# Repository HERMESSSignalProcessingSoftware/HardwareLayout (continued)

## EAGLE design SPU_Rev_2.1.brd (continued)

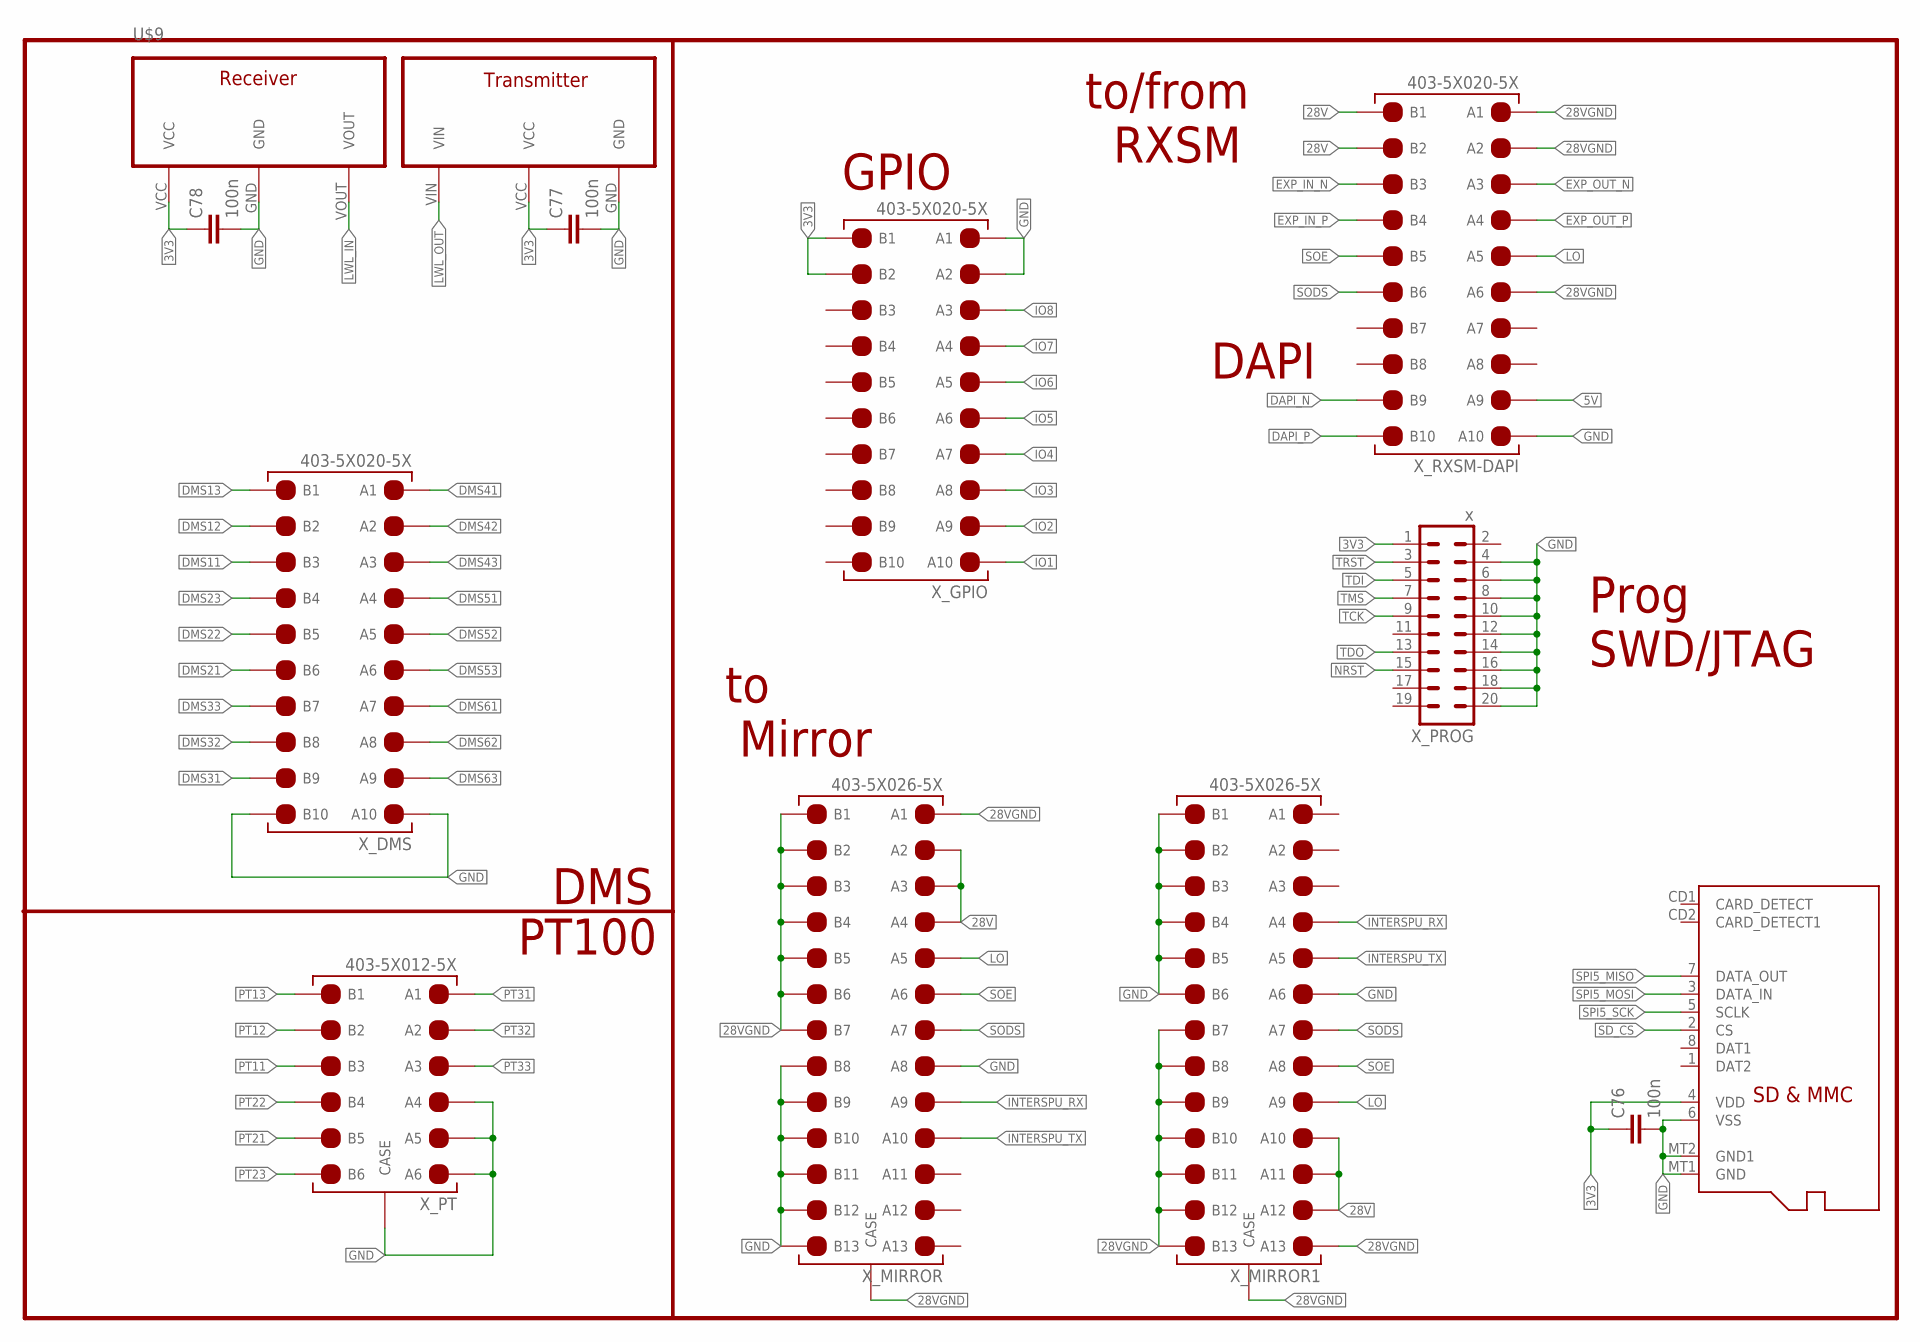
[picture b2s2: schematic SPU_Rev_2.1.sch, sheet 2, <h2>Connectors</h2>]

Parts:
C76: 100n; 0603-CAP
C77, C78: 100n; C1206
U$7: MICROSD
U$8: PLT131PLT131-T1; PLT131-T1
U$9: PLR135; PLR135-T1
X_DMS: 403-5X020-5X
X_GPIO: 403-5X020-5X
X_MIRROR, X_MIRROR1: 403-5X026-5X
X_PROG: x; MA10-2
X_PT: 403-5X012-5X
X_RXSM-DAPI: 403-5X020-5X

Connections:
3V3: C76.1, C77.1, C78.1, U$7.4 (VDD), U$8.VCC, U$9.VCC, X_GPIO.P$B1 (B1), X_GPIO.P$B2 (B2), X_PROG.1; also elsewhere on the board
5V: X_RXSM-DAPI.P$A9 (A9); also elsewhere on the board
28V: X_MIRROR.P$A2 (A2), X_MIRROR.P$A3 (A3), X_MIRROR.P$A4 (A4), X_MIRROR1.P$A10 (A10), X_MIRROR1.P$A11 (A11), X_MIRROR1.P$A12 (A12), X_RXSM-DAPI.P$B1 (B1), X_RXSM-DAPI.P$B2 (B2); also elsewhere on the board
28VGND: X_MIRROR.P$A1 (A1), X_MIRROR.P$B1 (B1), X_MIRROR.P$B2 (B2), X_MIRROR.P$B3 (B3), X_MIRROR.P$B4 (B4), X_MIRROR.P$B5 (B5), X_MIRROR.P$B6 (B6), X_MIRROR.P$B7 (B7), X_MIRROR.P$BL1 (CASE), X_MIRROR.P$BL2 (CASE), X_MIRROR.P$BL3 (CASE), X_MIRROR.P$BL4 (CASE), X_MIRROR1.P$A13 (A13), X_MIRROR1.P$B7 (B7), X_MIRROR1.P$B8 (B8), X_MIRROR1.P$B9 (B9), X_MIRROR1.P$B10 (B10), X_MIRROR1.P$B11 (B11), X_MIRROR1.P$B12 (B12), X_MIRROR1.P$B13 (B13), X_MIRROR1.P$BL1 (CASE), X_MIRROR1.P$BL2 (CASE), X_MIRROR1.P$BL3 (CASE), X_MIRROR1.P$BL4 (CASE), X_RXSM-DAPI.P$A1 (A1), X_RXSM-DAPI.P$A2 (A2), X_RXSM-DAPI.P$A6 (A6); also elsewhere on the board
DAPI_N: X_RXSM-DAPI.P$B9 (B9); also elsewhere on the board
DAPI_P: X_RXSM-DAPI.P$B10 (B10); also elsewhere on the board
DMS11: X_DMS.P$B3 (B3); also elsewhere on the board
DMS12: X_DMS.P$B2 (B2); also elsewhere on the board
DMS13: X_DMS.P$B1 (B1); also elsewhere on the board
DMS21: X_DMS.P$B6 (B6); also elsewhere on the board
DMS22: X_DMS.P$B5 (B5); also elsewhere on the board
DMS23: X_DMS.P$B4 (B4); also elsewhere on the board
DMS31: X_DMS.P$B9 (B9); also elsewhere on the board
DMS32: X_DMS.P$B8 (B8); also elsewhere on the board
DMS33: X_DMS.P$B7 (B7); also elsewhere on the board
DMS41: X_DMS.P$A1 (A1); also elsewhere on the board
DMS42: X_DMS.P$A2 (A2); also elsewhere on the board
DMS43: X_DMS.P$A3 (A3); also elsewhere on the board
DMS51: X_DMS.P$A4 (A4); also elsewhere on the board
DMS52: X_DMS.P$A5 (A5); also elsewhere on the board
DMS53: X_DMS.P$A6 (A6); also elsewhere on the board
DMS61: X_DMS.P$A7 (A7); also elsewhere on the board
DMS62: X_DMS.P$A8 (A8); also elsewhere on the board
DMS63: X_DMS.P$A9 (A9); also elsewhere on the board
EXP_IN_N: X_RXSM-DAPI.P$B3 (B3); also elsewhere on the board
EXP_IN_P: X_RXSM-DAPI.P$B4 (B4); also elsewhere on the board
EXP_OUT_N: X_RXSM-DAPI.P$A3 (A3); also elsewhere on the board
EXP_OUT_P: X_RXSM-DAPI.P$A4 (A4); also elsewhere on the board
GND: C76.2, C77.2, C78.2, U$7.6 (VSS), U$7.MT1 (GND), U$7.MT2 (GND1), U$8.GND, U$9.GND, X_DMS.P$A10 (A10), X_DMS.P$B10 (B10), X_GPIO.P$A1 (A1), X_GPIO.P$A2 (A2), X_MIRROR.P$A8 (A8), X_MIRROR.P$B8 (B8), X_MIRROR.P$B9 (B9), X_MIRROR.P$B10 (B10), X_MIRROR.P$B11 (B11), X_MIRROR.P$B12 (B12), X_MIRROR.P$B13 (B13), X_MIRROR1.P$A6 (A6), X_MIRROR1.P$B1 (B1), X_MIRROR1.P$B2 (B2), X_MIRROR1.P$B3 (B3), X_MIRROR1.P$B4 (B4), X_MIRROR1.P$B5 (B5), X_MIRROR1.P$B6 (B6), X_PROG.4, X_PROG.6, X_PROG.8, X_PROG.10, X_PROG.12, X_PROG.14, X_PROG.16, X_PROG.18, X_PROG.20, X_PT.P$A4 (A4), X_PT.P$A5 (A5), X_PT.P$A6 (A6), X_PT.P$BL1 (CASE), X_PT.P$BL2 (CASE), X_PT.P$BL3 (CASE), X_PT.P$BL4 (CASE), X_RXSM-DAPI.P$A10 (A10); also elsewhere on the board
INTERSPU_RX: X_MIRROR.P$A9 (A9), X_MIRROR1.P$A4 (A4); also elsewhere on the board
INTERSPU_TX: X_MIRROR.P$A10 (A10), X_MIRROR1.P$A5 (A5); also elsewhere on the board
IO1: X_GPIO.P$A10 (A10); also elsewhere on the board
IO2: X_GPIO.P$A9 (A9); also elsewhere on the board
IO3: X_GPIO.P$A8 (A8); also elsewhere on the board
IO4: X_GPIO.P$A7 (A7); also elsewhere on the board
IO5: X_GPIO.P$A6 (A6); also elsewhere on the board
IO6: X_GPIO.P$A5 (A5); also elsewhere on the board
IO7: X_GPIO.P$A4 (A4); also elsewhere on the board
IO8: X_GPIO.P$A3 (A3); also elsewhere on the board
LO: X_MIRROR.P$A5 (A5), X_MIRROR1.P$A9 (A9), X_RXSM-DAPI.P$A5 (A5); also elsewhere on the board
LWL_IN: U$9.VOUT; also elsewhere on the board
LWL_OUT: U$8.VIN; also elsewhere on the board
NRST: X_PROG.15; also elsewhere on the board
PT11: X_PT.P$B3 (B3); also elsewhere on the board
PT12: X_PT.P$B2 (B2); also elsewhere on the board
PT13: X_PT.P$B1 (B1); also elsewhere on the board
PT21: X_PT.P$B5 (B5); also elsewhere on the board
PT22: X_PT.P$B4 (B4); also elsewhere on the board
PT23: X_PT.P$B6 (B6); also elsewhere on the board
PT31: X_PT.P$A1 (A1); also elsewhere on the board
PT32: X_PT.P$A2 (A2); also elsewhere on the board
PT33: X_PT.P$A3 (A3); also elsewhere on the board
SD_CS: U$7.2 (CS); also elsewhere on the board
SODS: X_MIRROR.P$A7 (A7), X_MIRROR1.P$A7 (A7), X_RXSM-DAPI.P$B6 (B6); also elsewhere on the board
SOE: X_MIRROR.P$A6 (A6), X_MIRROR1.P$A8 (A8), X_RXSM-DAPI.P$B5 (B5); also elsewhere on the board
SPI5_MISO: U$7.7 (DATA_OUT); also elsewhere on the board
SPI5_MOSI: U$7.3 (DATA_IN); also elsewhere on the board
SPI5_SCK: U$7.5 (SCLK); also elsewhere on the board
TCK: X_PROG.9; also elsewhere on the board
TDI: X_PROG.5; also elsewhere on the board
TDO: X_PROG.13; also elsewhere on the board
TMS: X_PROG.7; also elsewhere on the board
TRST: X_PROG.3; also elsewhere on the board

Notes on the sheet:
DMS
PT100
DAPI
to/from RXSM
to Mirror
Prog SWD/JTAG
GPIO

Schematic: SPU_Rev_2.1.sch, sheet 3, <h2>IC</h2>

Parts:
C1, C2: 22p; C0603
C3, C5, C6, C7, C8, C9, C10, C12, C13, C14, C15, C19, C21, C22, C23, C24, C25, C27, C45, C46, C47, C48, C50, C51, C53, C54, C55, C57, C58, C59: 100n; C0603
C4, C11, C20, C26, C49, C56: 1u; C1206
C28, C29, C30, C31, C32, C33, C34, C35, C36, C37, C42, C43, C75: 100n; C0805
C38, C39, C40, C41, C60, C61, C62, C64, C65, C66, C67, C68, C69, C70, C71, C72, C73: 10u; E/7260-38W
C44: ~0; C0805
C52, C74: 10n; C0805
C_AVDD_PT1, C_AVDD_PT2, C_AVDD_PT3: 100n; C0603
C_DVDD_PT1, C_DVDD_PT2, C_DVDD_PT3: 100n; C0603
C_ICM1_PT1, C_ICM1_PT2, C_ICM2_PT1, C_ICM2_PT2: C-EUC0603; C0603
C_ICM1_PT3, C_ICM2_PT3: 4n7; C0603
C_IDIFF_PT1, C_IDIFF_PT2: C-EUC0603; C0603
C_IDIFF_PT3: 47n; C0603
C_RCM1_PT1, C_RCM1_PT2, C_RCM1_PT3, C_RCM2_PT1, C_RCM2_PT2, C_RCM2_PT3: C-EUC0603; C0603
C_RDIFF_PT1, C_RDIFF_PT2: C-EUC0603; C0603
C_RDIFF_PT3: 100n; C0603
C_VREF_PT1, C_VREF_PT2, C_VREF_PT3: 1u; C0603
D1, D2, D5, D6: 6V; DMELF
D3, D4, D7, D8, D9, D10, D11, D12: 3V6; DMELF
Q1: 12MHz; SM49
R1, R2, R8, R30, R36, R37, R43, R44, R50, R51, R57, R58: 4k7; R0603
R3, R31, R38, R45, R52, R59: 47; R0603
R4, R5, R32, R33, R39, R40, R46, R47, R53, R54, R60, R61: 40 1%; R0805
R6, R7, R34, R35, R41, R42, R48, R49, R55, R56, R62, R63: 1k 0.1%; R0805
R10, R15: 500; R0805
R11: 3k; R0805
R12: 2k; R0805
R13: 4k7; R0805
R14: 7k5; R0805
R16, R17: 3k3; R0805
R22: 100k; R0805
R23: 1k; R0805
R24, R25: ?; R0805
RN11: 3k; EXBS8V
RN12: 1k; EXBS8V
RN_A_PT1, RN_A_PT2, RN_A_PT3: 47; 0603-ARC
RN_B_PT1, RN_B_PT2, RN_B_PT3: 47; 0603-ARC
RN_DMS1, RN_DMS2, RN_DMS3, RN_DMS4, RN_DMS5, RN_DMS6: 47; 0603-ARC
R_I1_PT1, R_I1_PT2, R_I2_PT1, R_I2_PT2: R-EU_R0603; R0603
R_I1_PT3, R_I2_PT3: 5k; R0603
R_R1_PT1, R_R1_PT2, R_R2_PT1, R_R2_PT2: R-EU_R0603; R0603
R_R1_PT3: 3k16; R0603
R_R2_PT3: inf; R0603
R_REF_PT1, R_REF_PT2: R-EU_R0603; R0603
R_REF_PT3: 1k62; R0603
U$1, U$2, U$3, U$4, U$5, U$6: COMMON_MODE_CHOKE
U_7805: LM78L05ACMX/NOPB; SOIC8
U_ADC_DMS1, U_ADC_DMS2, U_ADC_DMS3, U_ADC_DMS4, U_ADC_DMS5, U_ADC_DMS6: ADS1147TSSOP20; TSSOP20
U_ADC_PT1, U_ADC_PT2, U_ADC_PT3: ADS1147TSSOP20; TSSOP20
U_ADR366_3: ADR366WAUJZ; SOT23-5
U_CH340G: CH340G; SOIC16
U_FLASH1, U_FLASH2: S70FL01GS; SO16
U_LT1528: LT1528; Q5-DD
U_MAX488: MAX488CSA; SO08
U_OPTO_1, U_OPTO_2, U_OPTO_3: MOCD207MSOIC-8; SOIC127P594X363-8N
U_TRACODCDC: THN10-2411WIR; THL_20WI_SERIES

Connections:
3V3: C3.1, C5.1, C9.1, C10.1, C15.1, C19.1, C24.1, C25.1, C28.1, C29.1, C30.1, C31.1, C32.1, C33.1, C37.2, C41.+, C47.1, C48.1, C54.1, C55.1, C67.+, C68.+, C69.+, C70.+, C71.+, C72.+, C73.+, C_AVDD_PT1.1, C_AVDD_PT2.1, C_AVDD_PT3.1, C_DVDD_PT1.1, C_DVDD_PT2.1, C_DVDD_PT3.1, R1.1, R2.2, R6.2, R8.1, R13.2, R30.2, R34.2, R36.1, R37.2, R41.2, R43.1, R44.2, R48.2, R50.1, R51.2, R55.2, R57.1, R58.2, R62.2, RN12.1, RN12.2 (1), RN12.3 (1), RN12.4 (1), RN_A_PT1.8 (2), RN_A_PT2.8 (2), RN_A_PT3.8 (2), RN_B_PT1.6 (2), RN_B_PT2.6 (2), RN_B_PT3.6 (2), U$1.P$2 (2), U$2.P$2 (2), U$3.P$2 (2), U$4.P$2 (2), U$5.P$2 (2), U$6.P$2 (2), U_ADC_DMS1.1 (DVDD), U_ADC_DMS1.14 (AVDD), U_ADC_DMS2.1 (DVDD), U_ADC_DMS2.14 (AVDD), U_ADC_DMS3.1 (DVDD), U_ADC_DMS3.14 (AVDD), U_ADC_DMS4.1 (DVDD), U_ADC_DMS4.14 (AVDD), U_ADC_DMS5.1 (DVDD), U_ADC_DMS5.14 (AVDD), U_ADC_DMS6.1 (DVDD), U_ADC_DMS6.14 (AVDD), U_ADC_PT1.1 (DVDD), U_ADC_PT1.14 (AVDD), U_ADC_PT2.1 (DVDD), U_ADC_PT2.14 (AVDD), U_ADC_PT3.1 (DVDD), U_ADC_PT3.14 (AVDD), U_CH340G.4 (V3), U_CH340G.16 (VCC), U_FLASH1.2 (VCC), U_FLASH2.2 (VCC), U_LT1528.1 (OUT), U_LT1528.2 (SENSE); also elsewhere on the board
3V3REF: C74.2, C75.2, R24.2, U_ADR366_3.4 (VOUT); also elsewhere on the board
5V: C35.2, C36.2, C39.+, C40.+, C52.2, C64.+, C65.+, C66.+, U_ADR366_3.3 (VIN), U_LT1528.4 (SHDN), U_LT1528.5 (IN), U_TRACODCDC.3 (+VOUT); also elsewhere on the board
5V-28V: C43.1, R14.2, R16.1, U_7805.1 (VOUT), U_MAX488.1 (VCC); also elsewhere on the board
28V: C34.2, C38.+, C42.2, C60.+, C61.+, C62.+, RN11.1, RN11.2 (1), RN11.3 (1), RN11.4 (1), U_7805.8 (VIN), U_TRACODCDC.1 (+VIN); also elsewhere on the board
28VGND: C34.1, C38.-, C42.1, C43.2, C44.2, C60.-, C61.-, C62.-, D5.A, D6.A, R11.1, R17.1, U_7805.2 (GND), U_7805.3 (GND), U_7805.6 (GND), U_7805.7 (GND), U_MAX488.4 (GND), U_OPTO_3.5 (EMT2), U_TRACODCDC.2 (-VIN); also elsewhere on the board
!CS!_DMS1: R3.2; also elsewhere on the board
!CS!_DMS2: R31.2; also elsewhere on the board
!CS!_DMS3: R38.2; also elsewhere on the board
!CS!_DMS4: R45.2; also elsewhere on the board
!CS!_DMS5: R52.2; also elsewhere on the board
!CS!_DMS6: R59.2; also elsewhere on the board
!CS!_PT1: RN_B_PT1.7 (2); also elsewhere on the board
!CS!_PT2: RN_B_PT2.7 (2); also elsewhere on the board
!CS!_PT3: RN_B_PT3.7 (2); also elsewhere on the board
!DRDY!_DMS1: RN_DMS1.5 (2); also elsewhere on the board
!DRDY!_DMS2: RN_DMS2.5 (2); also elsewhere on the board
!DRDY!_DMS3: RN_DMS3.5 (2); also elsewhere on the board
!DRDY!_DMS4: RN_DMS4.5 (2); also elsewhere on the board
!DRDY!_DMS5: RN_DMS5.5 (2); also elsewhere on the board
!DRDY!_DMS6: RN_DMS6.5 (2); also elsewhere on the board
!DRDY!_PT1: RN_B_PT1.8 (2); also elsewhere on the board
!DRDY!_PT2: RN_B_PT2.8 (2); also elsewhere on the board
!DRDY!_PT3: RN_B_PT3.8 (2); also elsewhere on the board
DAPI_N: D1.C, U_CH340G.6 (D-); also elsewhere on the board
DAPI_P: D2.C, U_CH340G.5 (D+); also elsewhere on the board
DAPI_RX: D4.C, U_CH340G.2 (TX); also elsewhere on the board
DAPI_TX: D3.C, U_CH340G.3 (RX); also elsewhere on the board
DMS11: U$2.P$1 (1); also elsewhere on the board
DMS12: U$2.P$3 (3); also elsewhere on the board
DMS13: U$2.P$5 (5); also elsewhere on the board
DMS21: U$1.P$1 (1); also elsewhere on the board
DMS22: U$1.P$3 (3); also elsewhere on the board
DMS23: U$1.P$5 (5); also elsewhere on the board
DMS31: U$3.P$1 (1); also elsewhere on the board
DMS32: U$3.P$3 (3); also elsewhere on the board
DMS33: U$3.P$5 (5); also elsewhere on the board
DMS41: U$4.P$1 (1); also elsewhere on the board
DMS42: U$4.P$3 (3); also elsewhere on the board
DMS43: U$4.P$5 (5); also elsewhere on the board
DMS51: U$5.P$1 (1); also elsewhere on the board
DMS52: U$5.P$3 (3); also elsewhere on the board
DMS53: U$5.P$5 (5); also elsewhere on the board
DMS61: U$6.P$1 (1); also elsewhere on the board
DMS62: U$6.P$3 (3); also elsewhere on the board
DMS63: U$6.P$5 (5); also elsewhere on the board
EXP_IN: D5.C, U_MAX488.2 (RO), U_OPTO_3.1 (A1)
EXP_IN_N: R15.1, R17.2, U_MAX488.7 (B); also elsewhere on the board
EXP_IN_OPT: D10.C, R13.1, U_OPTO_3.8 (COL1); also elsewhere on the board
EXP_IN_P: R10.2, R16.2, U_MAX488.8 (A); also elsewhere on the board
EXP_OUT: D6.C, R14.1, U_MAX488.3 (DI), U_OPTO_3.6 (COL2)
EXP_OUT_N: U_MAX488.6 (Z); also elsewhere on the board
EXP_OUT_OPT: U_OPTO_3.3 (A2); also elsewhere on the board
EXP_OUT_P: U_MAX488.5 (Y); also elsewhere on the board
FL_1_CS1: U_FLASH1.7 (CS1); also elsewhere on the board
FL_1_CS2: U_FLASH1.6 (CS2); also elsewhere on the board
FL_1_HLD: U_FLASH1.1 (HOLD); also elsewhere on the board
FL_1_RES: U_FLASH1.3 (RESET); also elsewhere on the board
FL_1_WP: U_FLASH1.9 (WP); also elsewhere on the board
FL_2_CS1: U_FLASH2.7 (CS1); also elsewhere on the board
FL_2_CS2: U_FLASH2.6 (CS2); also elsewhere on the board
FL_2_HLD: U_FLASH2.1 (HOLD); also elsewhere on the board
FL_2_RES: U_FLASH2.3 (RESET); also elsewhere on the board
FL_2_WP: U_FLASH2.9 (WP); also elsewhere on the board
GND: C1.2, C2.2, C3.2, C4.2, C5.2, C6.1, C8.2, C9.2, C10.2, C11.2, C12.1, C14.2, C15.2, C19.2, C20.2, C21.1, C23.2, C24.2, C25.2, C26.2, C27.1, C28.2, C29.2, C30.2, C31.2, C32.2, C33.2, C35.1, C36.1, C37.1, C39.-, C40.-, C41.-, C46.2, C47.2, C48.2, C49.2, C50.1, C52.1, C53.2, C54.2, C55.2, C56.2, C57.1, C59.2, C64.-, C65.-, C66.-, C67.-, C68.-, C69.-, C70.-, C71.-, C72.-, C73.-, C74.1, C75.1, C_AVDD_PT1.2, C_AVDD_PT2.2, C_AVDD_PT3.2, C_DVDD_PT1.2, C_DVDD_PT2.2, C_DVDD_PT3.2, C_ICM1_PT1.1, C_ICM1_PT2.1, C_ICM1_PT3.1, C_ICM2_PT1.2, C_ICM2_PT2.2, C_ICM2_PT3.2, C_RCM1_PT1.1, C_RCM1_PT2.1, C_RCM1_PT3.1, C_RCM2_PT1.2, C_RCM2_PT2.2, C_RCM2_PT3.2, C_VREF_PT1.2, C_VREF_PT2.2, C_VREF_PT3.2, D1.A, D2.A, D3.A, D4.A, D7.A, D8.A, D9.A, D10.A, D11.A, D12.A, R7.2, R12.1, R23.1, R35.2, R42.2, R49.2, R56.2, R63.2, RN_B_PT1.4 (1), RN_B_PT1.5 (2), RN_B_PT2.4 (1), RN_B_PT2.5 (2), RN_B_PT3.4 (1), RN_B_PT3.5 (2), R_R2_PT1.2, R_R2_PT2.2, R_R2_PT3.2, R_REF_PT1.1, R_REF_PT2.1, R_REF_PT3.1, U$1.P$6 (6), U$2.P$6 (6), U$3.P$6 (6), U$4.P$6 (6), U$5.P$6 (6), U$6.P$6 (6), U_ADC_DMS1.2 (DGND/DSS), U_ADC_DMS1.3 (CLK), U_ADC_DMS1.8 (VREFCOM), U_ADC_DMS1.13 (AVSS), U_ADC_DMS2.2 (DGND/DSS), U_ADC_DMS2.3 (CLK), U_ADC_DMS2.8 (VREFCOM), U_ADC_DMS2.13 (AVSS), U_ADC_DMS3.2 (DGND/DSS), U_ADC_DMS3.3 (CLK), U_ADC_DMS3.8 (VREFCOM), U_ADC_DMS3.13 (AVSS), U_ADC_DMS4.2 (DGND/DSS), U_ADC_DMS4.3 (CLK), U_ADC_DMS4.8 (VREFCOM), U_ADC_DMS4.13 (AVSS), U_ADC_DMS5.2 (DGND/DSS), U_ADC_DMS5.3 (CLK), U_ADC_DMS5.8 (VREFCOM), U_ADC_DMS5.13 (AVSS), U_ADC_DMS6.2 (DGND/DSS), U_ADC_DMS6.3 (CLK), U_ADC_DMS6.8 (VREFCOM), U_ADC_DMS6.13 (AVSS), U_ADC_PT1.2 (DGND/DSS), U_ADC_PT1.3 (CLK), U_ADC_PT1.8 (VREFCOM), U_ADC_PT1.13 (AVSS), U_ADC_PT2.2 (DGND/DSS), U_ADC_PT2.3 (CLK), U_ADC_PT2.8 (VREFCOM), U_ADC_PT2.13 (AVSS), U_ADC_PT3.2 (DGND/DSS), U_ADC_PT3.3 (CLK), U_ADC_PT3.8 (VREFCOM), U_ADC_PT3.13 (AVSS), U_ADR366_3.2 (GND), U_CH340G.1 (GND), U_FLASH1.10 (VSS), U_FLASH2.10 (VSS), U_LT1528.3 (GND), U_LT1528.6 (GND), U_OPTO_1.5 (EMT2), U_OPTO_1.7 (EMT1), U_OPTO_2.5 (EMT2), U_OPTO_2.7 (EMT1), U_OPTO_3.7 (EMT1), U_TRACODCDC.5 (-VOUT); also elsewhere on the board
INTERSPU_RX: D11.C; also elsewhere on the board
INTERSPU_TX: D12.C; also elsewhere on the board
LO: U_OPTO_2.2 (C1); also elsewhere on the board
LO_OPT: D7.C, RN12.6 (2), U_OPTO_2.8 (COL1); also elsewhere on the board
unnamed: C2.1, Q1.2, U_CH340G.8 (XO)
unnamed: R2.1, U_ADC_DMS1.15 (START)
unnamed: C1.1, Q1.1, U_CH340G.7 (XI)
unnamed: C_RCM2_PT2.1, C_RDIFF_PT2.2, R_R2_PT2.1, U_ADC_PT2.6 (REFN0/GPIO1)
unnamed: C_RCM1_PT2.2, C_RDIFF_PT2.1, R_R1_PT2.1, U_ADC_PT2.5 (REFP0/GPIO0)
unnamed: C_ICM2_PT2.1, C_IDIFF_PT2.2, R_I2_PT2.1, U_ADC_PT2.11 (AIN2/IEXC/GPIO2)
unnamed: C12.2, C13.1, R32.1, U_ADC_DMS2.9 (AIN0/IEXC)
unnamed: C_VREF_PT1.1, U_ADC_PT1.7 (VREFOUT)
unnamed: C_ICM2_PT1.1, C_IDIFF_PT1.2, R_I2_PT1.1, U_ADC_PT1.11 (AIN2/IEXC/GPIO2)
unnamed: RN_DMS1.1, U_ADC_DMS1.20 (SCLK)
unnamed: C13.2, C14.1, R33.1, U_ADC_DMS2.10 (AIN1/IEXC)
unnamed: R33.2, R34.1, R35.1
unnamed: C_RCM2_PT1.1, C_RDIFF_PT1.2, R_R2_PT1.1, U_ADC_PT1.6 (REFN0/GPIO1)
unnamed: C_RCM1_PT1.2, C_RDIFF_PT1.1, R_R1_PT1.1, U_ADC_PT1.5 (REFP0/GPIO0)
unnamed: C_ICM1_PT1.2, C_IDIFF_PT1.1, R_I1_PT1.1, U_ADC_PT1.10 (AIN1/IEXC)
unnamed: RN_A_PT1.2 (1), U_ADC_PT1.20 (SCLK)
unnamed 101: U_TRACODCDC.4 (TRIM); also elsewhere on the board
unnamed: RN_A_PT1.3 (1), U_ADC_PT1.19 (DIN)
unnamed: RN_A_PT1.4 (1), U_ADC_PT1.18 (DOUT/!DRDY)
unnamed: C_ICM1_PT2.2, C_IDIFF_PT2.1, R_I1_PT2.1, U_ADC_PT2.10 (AIN1/IEXC)
unnamed: C_VREF_PT2.1, U_ADC_PT2.7 (VREFOUT)
unnamed: RN_A_PT2.2 (1), U_ADC_PT2.20 (SCLK)
unnamed: RN_B_PT1.1, U_ADC_PT1.17 (!DRDY)
unnamed: RN_B_PT1.2 (1), U_ADC_PT1.16 (!CS)
unnamed: RN_B_PT1.3 (1), U_ADC_PT1.15 (START)
unnamed: RN_A_PT2.3 (1), U_ADC_PT2.19 (DIN)
unnamed: RN_A_PT2.4 (1), U_ADC_PT2.18 (DOUT/!DRDY)
unnamed: RN_B_PT2.1, U_ADC_PT2.17 (!DRDY)
unnamed: RN_B_PT2.2 (1), U_ADC_PT2.16 (!CS)
unnamed: RN_B_PT2.3 (1), U_ADC_PT2.15 (START)
unnamed: C_RCM2_PT3.1, C_RDIFF_PT3.2, R_R2_PT3.1, U_ADC_PT3.6 (REFN0/GPIO1)
unnamed: C_RCM1_PT3.2, C_RDIFF_PT3.1, R_R1_PT3.1, U_ADC_PT3.5 (REFP0/GPIO0)
unnamed: RN11.6 (2), U_OPTO_1.1 (A1)
unnamed: RN11.5 (2), U_OPTO_1.3 (A2)
unnamed: R12.2, U_OPTO_3.4 (C2)
unnamed: RN12.5 (2), U_OPTO_2.6 (COL2)
unnamed: RN11.8 (2), U_OPTO_2.1 (A1)
unnamed: RN11.7 (2), U_OPTO_2.3 (A2)
unnamed: R11.2, U_OPTO_3.2 (C1)
unnamed: C44.1, R10.1, R15.2
unnamed: C_ICM2_PT3.1, C_IDIFF_PT3.2, R_I2_PT3.1, U_ADC_PT3.11 (AIN2/IEXC/GPIO2)
unnamed: C_ICM1_PT3.2, C_IDIFF_PT3.1, R_I1_PT3.1, U_ADC_PT3.10 (AIN1/IEXC)
unnamed: C_VREF_PT3.1, U_ADC_PT3.7 (VREFOUT)
unnamed: RN_A_PT3.2 (1), U_ADC_PT3.20 (SCLK)
unnamed: RN_A_PT3.3 (1), U_ADC_PT3.19 (DIN)
unnamed: RN_A_PT3.4 (1), U_ADC_PT3.18 (DOUT/!DRDY)
unnamed: RN_B_PT3.1, U_ADC_PT3.17 (!DRDY)
unnamed: RN_B_PT3.2 (1), U_ADC_PT3.16 (!CS)
unnamed: RN_B_PT3.3 (1), U_ADC_PT3.15 (START)
unnamed: RN_A_PT3.1, U_ADC_PT3.4 (!RESET)
unnamed: RN_A_PT2.1, U_ADC_PT2.4 (!RESET)
unnamed: RN_A_PT1.1, U_ADC_PT1.4 (!RESET)
unnamed: C11.1, U_ADC_DMS2.7 (VREFOUT)
unnamed: R22.1, U_ADR366_3.5 (TRIM)
unnamed: R22.2, R24.1, R25.2
unnamed: R23.2, R25.1
unnamed: R32.2, U$1.P$4 (4)
unnamed: R1.2, U_ADC_DMS1.4 (!RESET)
unnamed: RN_DMS1.2 (1), U_ADC_DMS1.19 (DIN)
unnamed: RN_DMS1.3 (1), U_ADC_DMS1.18 (DOUT/!DRDY)
unnamed: RN_DMS1.4 (1), U_ADC_DMS1.17 (!DRDY)
unnamed: R3.1, U_ADC_DMS1.16 (!CS)
unnamed: R8.2, U_ADC_DMS2.4 (!RESET)
unnamed: R30.1, U_ADC_DMS2.15 (START)
unnamed: C6.2, C7.1, R4.1, U_ADC_DMS1.9 (AIN0/IEXC)
unnamed: C7.2, C8.1, R5.1, U_ADC_DMS1.10 (AIN1/IEXC)
unnamed: R5.2, R6.1, R7.1
unnamed: C4.1, U_ADC_DMS1.7 (VREFOUT)
unnamed: R4.2, U$2.P$4 (4)
unnamed: RN_DMS2.1, U_ADC_DMS2.20 (SCLK)
unnamed: RN_DMS2.2 (1), U_ADC_DMS2.19 (DIN)
unnamed: RN_DMS2.3 (1), U_ADC_DMS2.18 (DOUT/!DRDY)
unnamed: RN_DMS2.4 (1), U_ADC_DMS2.17 (!DRDY)
unnamed: R31.1, U_ADC_DMS2.16 (!CS)
unnamed: C21.2, C22.1, R39.1, U_ADC_DMS3.9 (AIN0/IEXC)
unnamed: C22.2, C23.1, R40.1, U_ADC_DMS3.10 (AIN1/IEXC)
unnamed: R40.2, R41.1, R42.1
unnamed: C20.1, U_ADC_DMS3.7 (VREFOUT)
unnamed: R39.2, U$3.P$4 (4)
unnamed: R36.2, U_ADC_DMS3.4 (!RESET)
unnamed: R37.1, U_ADC_DMS3.15 (START)
unnamed: RN_DMS3.1, U_ADC_DMS3.20 (SCLK)
unnamed: RN_DMS3.2 (1), U_ADC_DMS3.19 (DIN)
unnamed: RN_DMS3.3 (1), U_ADC_DMS3.18 (DOUT/!DRDY)
unnamed: RN_DMS3.4 (1), U_ADC_DMS3.17 (!DRDY)
unnamed: R38.1, U_ADC_DMS3.16 (!CS)
unnamed: C27.2, C45.1, R46.1, U_ADC_DMS4.9 (AIN0/IEXC)
unnamed: C45.2, C46.1, R47.1, U_ADC_DMS4.10 (AIN1/IEXC)
unnamed: R47.2, R48.1, R49.1
unnamed: C26.1, U_ADC_DMS4.7 (VREFOUT)
unnamed: R46.2, U$4.P$4 (4)
unnamed: R43.2, U_ADC_DMS4.4 (!RESET)
unnamed: R44.1, U_ADC_DMS4.15 (START)
unnamed: RN_DMS4.1, U_ADC_DMS4.20 (SCLK)
unnamed: RN_DMS4.2 (1), U_ADC_DMS4.19 (DIN)
unnamed: RN_DMS4.3 (1), U_ADC_DMS4.18 (DOUT/!DRDY)
unnamed: RN_DMS4.4 (1), U_ADC_DMS4.17 (!DRDY)
unnamed: R45.1, U_ADC_DMS4.16 (!CS)
unnamed: C50.2, C51.1, R53.1, U_ADC_DMS5.9 (AIN0/IEXC)
unnamed: C51.2, C53.1, R54.1, U_ADC_DMS5.10 (AIN1/IEXC)
unnamed: R54.2, R55.1, R56.1
unnamed: C49.1, U_ADC_DMS5.7 (VREFOUT)
unnamed: R53.2, U$5.P$4 (4)
unnamed: R50.2, U_ADC_DMS5.4 (!RESET)
unnamed: R51.1, U_ADC_DMS5.15 (START)
unnamed: RN_DMS5.1, U_ADC_DMS5.20 (SCLK)
unnamed: RN_DMS5.2 (1), U_ADC_DMS5.19 (DIN)
unnamed: RN_DMS5.3 (1), U_ADC_DMS5.18 (DOUT/!DRDY)
unnamed: RN_DMS5.4 (1), U_ADC_DMS5.17 (!DRDY)
unnamed: R52.1, U_ADC_DMS5.16 (!CS)
unnamed: C57.2, C58.1, R60.1, U_ADC_DMS6.9 (AIN0/IEXC)
unnamed: C58.2, C59.1, R61.1, U_ADC_DMS6.10 (AIN1/IEXC)
unnamed: R61.2, R62.1, R63.1
unnamed: C56.1, U_ADC_DMS6.7 (VREFOUT)
unnamed: R60.2, U$6.P$4 (4)
unnamed: R57.2, U_ADC_DMS6.4 (!RESET)
unnamed: R58.1, U_ADC_DMS6.15 (START)
unnamed: RN_DMS6.1, U_ADC_DMS6.20 (SCLK)
unnamed: RN_DMS6.2 (1), U_ADC_DMS6.19 (DIN)
unnamed: RN_DMS6.3 (1), U_ADC_DMS6.18 (DOUT/!DRDY)
unnamed: RN_DMS6.4 (1), U_ADC_DMS6.17 (!DRDY)
unnamed: R59.1, U_ADC_DMS6.16 (!CS)
PT11: R_I1_PT1.2, U_ADC_PT1.9 (AIN0/IEXC); also elsewhere on the board
PT12: R_I2_PT1.2, U_ADC_PT1.12 (AIN3/IEXC/GPIO3); also elsewhere on the board
PT13: R_R1_PT1.2, R_REF_PT1.2; also elsewhere on the board
PT21: R_I1_PT2.2, U_ADC_PT2.9 (AIN0/IEXC); also elsewhere on the board
PT22: R_I2_PT2.2, U_ADC_PT2.12 (AIN3/IEXC/GPIO3); also elsewhere on the board
PT23: R_R1_PT2.2, R_REF_PT2.2; also elsewhere on the board
PT31: R_I1_PT3.2, U_ADC_PT3.9 (AIN0/IEXC); also elsewhere on the board
PT32: R_I2_PT3.2, U_ADC_PT3.12 (AIN3/IEXC/GPIO3); also elsewhere on the board
PT33: R_R1_PT3.2, R_REF_PT3.2; also elsewhere on the board
SODS: U_OPTO_1.2 (C1); also elsewhere on the board
SODS_OPT: D8.C, RN12.8 (2), U_OPTO_1.8 (COL1); also elsewhere on the board
SOE: U_OPTO_1.4 (C2); also elsewhere on the board
SOE_OPT: D9.C, RN12.7 (2), U_OPTO_1.6 (COL2); also elsewhere on the board
SPI2_MISO: U_FLASH2.8 (SO); also elsewhere on the board
SPI2_MOSI: U_FLASH2.15 (SI); also elsewhere on the board
SPI2_SCK: U_FLASH2.16 (SCK); also elsewhere on the board
SPI3_MISO: RN_A_PT1.5 (2), RN_A_PT2.5 (2), RN_A_PT3.5 (2); also elsewhere on the board
SPI3_MOSI: RN_A_PT1.6 (2), RN_A_PT2.6 (2), RN_A_PT3.6 (2); also elsewhere on the board
SPI3_SCK: RN_A_PT1.7 (2), RN_A_PT2.7 (2), RN_A_PT3.7 (2); also elsewhere on the board
SPI4_MISO: RN_DMS1.6 (2), RN_DMS2.6 (2), RN_DMS3.6 (2), RN_DMS4.6 (2), RN_DMS5.6 (2), RN_DMS6.6 (2); also elsewhere on the board
SPI4_MOSI: RN_DMS1.7 (2), RN_DMS2.7 (2), RN_DMS3.7 (2), RN_DMS4.7 (2), RN_DMS5.7 (2), RN_DMS6.7 (2); also elsewhere on the board
SPI4_SCK: RN_DMS1.8 (2), RN_DMS2.8 (2), RN_DMS3.8 (2), RN_DMS4.8 (2), RN_DMS5.8 (2), RN_DMS6.8 (2); also elsewhere on the board
SPI6_MISO: U_FLASH1.8 (SO); also elsewhere on the board
SPI6_MOSI: U_FLASH1.15 (SI); also elsewhere on the board
SPI6_SCK: U_FLASH1.16 (SCK); also elsewhere on the board

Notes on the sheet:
Ref voltage
FL1
FL2
ADCs
USB- UART
FLASH mem
V. Reg
LM78L05ACMX/NOPB
RS422 driver
logic side <-> RXSM side
Feinabgleich
Opto. isolation
Spike/ESD protection
Filter/Buffer caps.
all logic sided on this page
TODO for Rev 2.1 12 DMS-Paare (ergo 24 DMS), pro SPU 6 DMS-Paare 3 PT100 2 DMS pro ADC https://www.hbm.com/de/7163/die-wheatstonesche-brueckenschaltung-kurz-erklaert/ -> 3. Poisson H-Brücke
3dB attenuation @ 1989Hz
WE-SL3 SMT COMMON MODE LINE FILT

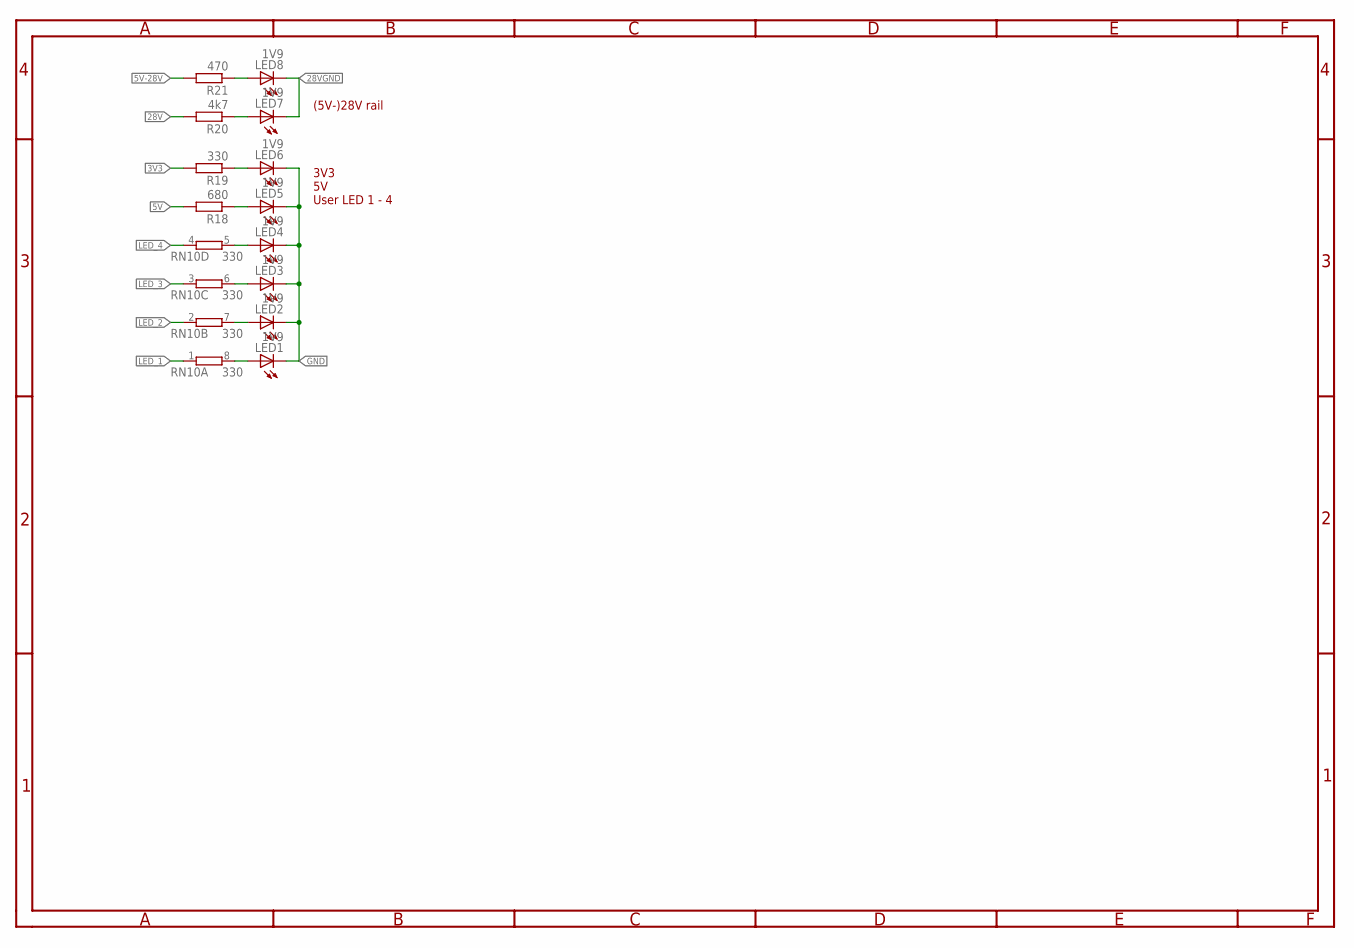
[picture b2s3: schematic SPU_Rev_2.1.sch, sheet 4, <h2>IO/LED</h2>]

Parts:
LED1, LED2, LED3, LED4, LED5, LED6, LED7, LED8: 1V9; CHIP-LED0805
R18: 680; R0805
R19: 330; R0805
R20: 4k7; R0805
R21: 470; R0805
RN10: 330; EXBS8V

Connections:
3V3: R19.2; also elsewhere on the board
5V: R18.2; also elsewhere on the board
5V-28V: R21.2; also elsewhere on the board
28V: R20.2; also elsewhere on the board
28VGND: LED7.C, LED8.C; also elsewhere on the board
GND: LED1.C, LED2.C, LED3.C, LED4.C, LED5.C, LED6.C; also elsewhere on the board
LED_1: RN10.1; also elsewhere on the board
LED_2: RN10.2 (1); also elsewhere on the board
LED_3: RN10.3 (1); also elsewhere on the board
LED_4: RN10.4 (1); also elsewhere on the board
unnamed: LED1.A, RN10.8 (2)
unnamed: LED2.A, RN10.7 (2)
unnamed: LED3.A, RN10.6 (2)
unnamed: LED4.A, RN10.5 (2)
unnamed: LED5.A, R18.1
unnamed: LED6.A, R19.1
unnamed: LED7.A, R20.1
unnamed: LED8.A, R21.1

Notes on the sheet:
(5V-)28V rail 3V3 5V User LED 1 - 4
